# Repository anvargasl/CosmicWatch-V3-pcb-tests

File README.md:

# CosmicWatch_V3_RP

Handling versions of CosmicWatch pcb design, reusing V2 DC to DC booster and implementing new peak detection designa.

## CosmicWatch_detector_v30

main project, bringing together the different versions of parts desinged for peak detection and power.

### DC-DC-booster

Reimplementing CosmicWatch-V2 Dc to DC booster for lower noise in the power line.

### Peak-Detector

Latest peak detector circuit implemented for tests.

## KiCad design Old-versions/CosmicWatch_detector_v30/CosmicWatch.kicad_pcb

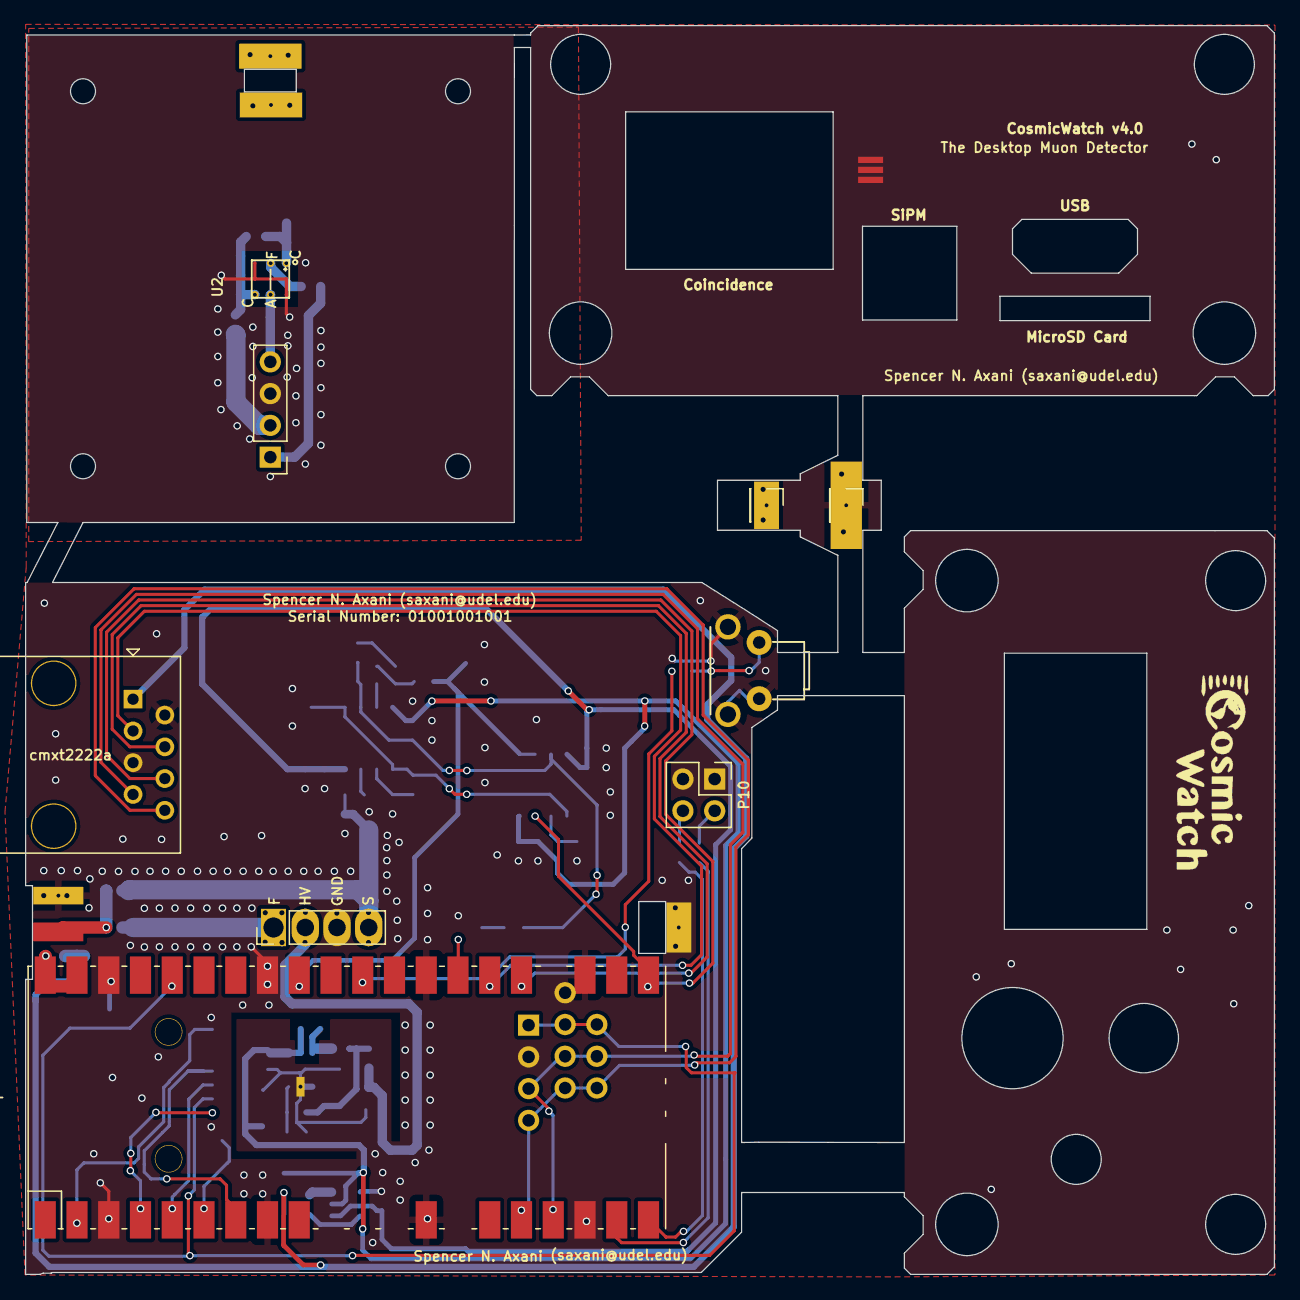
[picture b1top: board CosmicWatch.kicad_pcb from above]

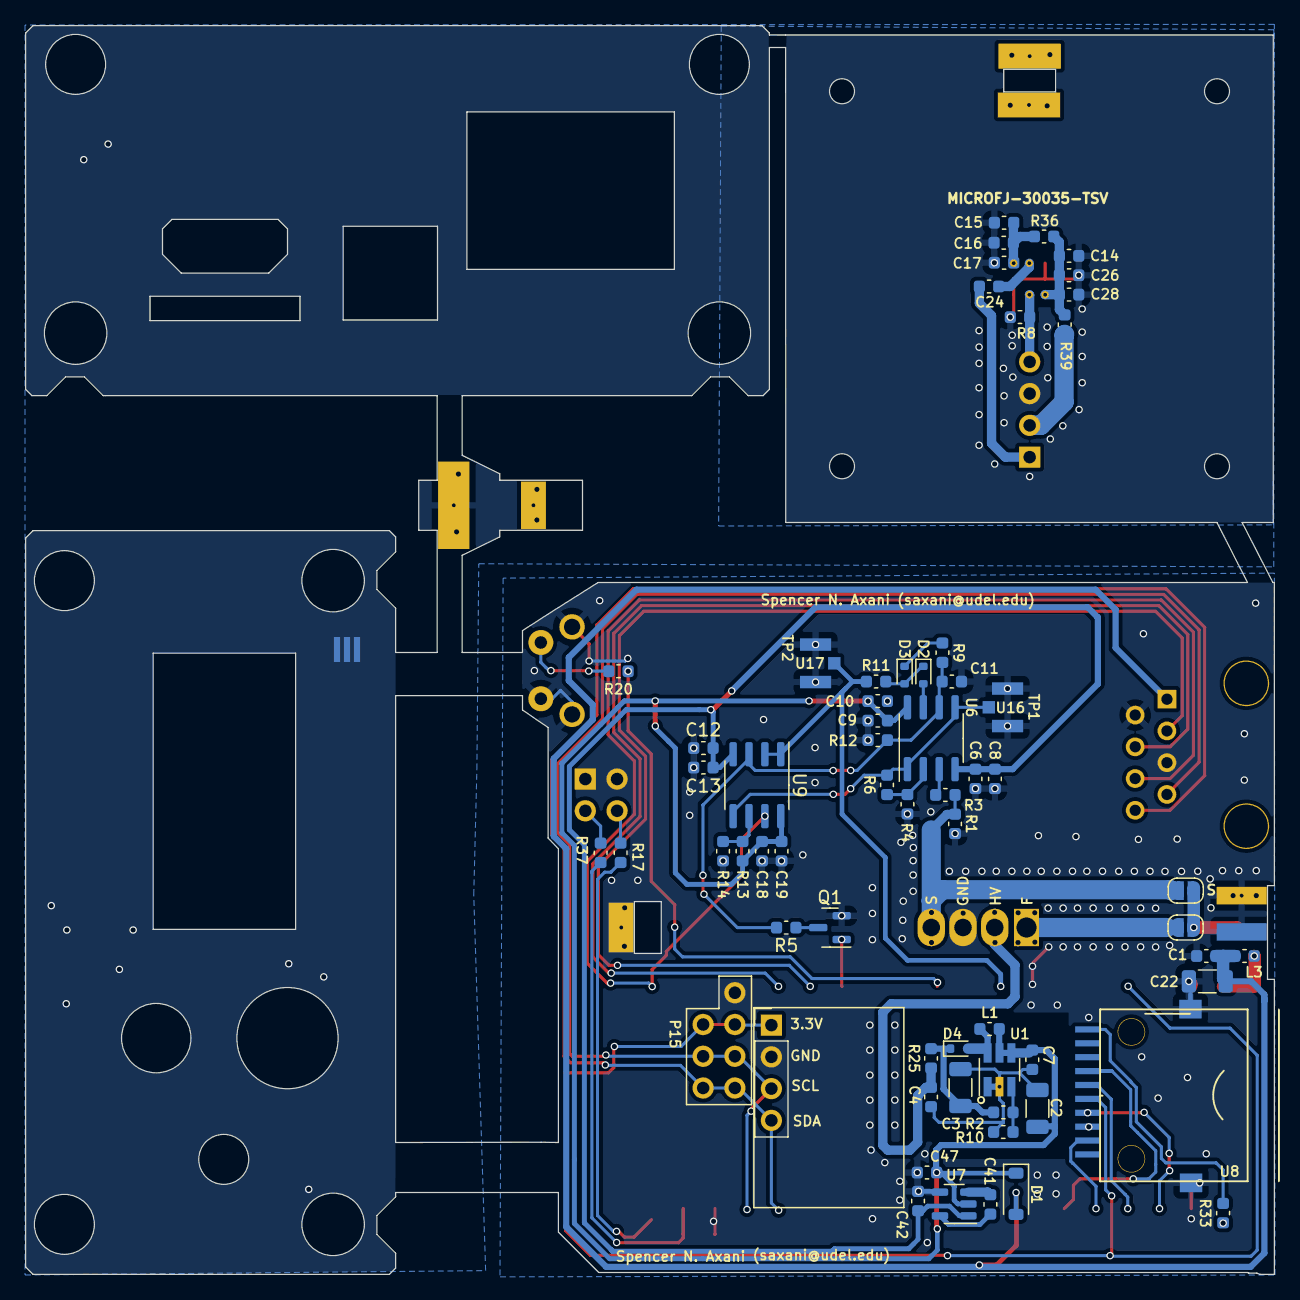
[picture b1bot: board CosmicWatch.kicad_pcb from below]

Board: 2 copper layers, 99.9 x 99.9 mm, 79 parts (65 on the bottom side), 49 nets.

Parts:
C1, C4, C47: 1uF; C_0603_1608Metric
C2: 4.7uF; C_1206_3216Metric
C3: 2.2uF; C_1206_3216Metric
C6, C12: 0.1uF; C_0603_1608Metric
C7, C8, C9, C13, C16, C18, C24, C26: 10nF; C_0603_1608Metric
C10, C19: 10n; C_0603_1608Metric
C11: 2nF; C_0603_1608Metric
C14, C17: 10p; C_0603_1608Metric
C15, C28: 100n; C_0603_1608Metric
C22: 6.8uF; C_1206_3216Metric
C41: C_0603_1608Metric
C42: 10uF; C_0603_1608Metric
D1: DIODE; D_SOD-123
D2, D3, D4: D_Schottky; D_SOD-523
J3: RJ45; RJ45_OST_PJ012-8P8CX_Vertical
L1: 15uH; C_0603_1608Metric
L3: INDUCTOR; C_0603_1608Metric
P1: CONN_01X04; PinHeader4_bigger_SiPM
P2: CONN_01X01; SiPM_PCB_Standoff
P3, P4: CONN_01X04; PinHeader_1x04_P2.54mm_Vertical
P5, P16: CONN_01X02; SolderJumper-2_P1.3mm_Open_RoundedPad1.0x1.5mm
P7, P8: CONN_01X01; GND_circle
P10: CONN_02X02; PinHeader_2x02_P2.54mm_Vertical
P11, P12, P13, P14: CONN_01X01; PinHeader_1x01_P2.54mm_Vertical
P15: CONN_02X04; PinHeader_2x04_P2.54mm_Vertical
P19: CONN_01X01; logo
Q1: 2N7002; SOT-23
R1: 47k; C_0603_1608Metric
R2: 147k; C_0603_1608Metric
R3: 49.9; C_0603_1608Metric
R4: 1k; C_0603_1608Metric
R5, R8, R36, R39: 10; C_0603_1608Metric
R6, R12, R13, R20, R33: 10k; C_0603_1608Metric
R9, R11, R14, R17, R25, R37: 100; C_0603_1608Metric
R10: 6.65k; C_0603_1608Metric
SW1: RESET; reset_button
U1: MAX5026; SOT-23-6_Handsoldering
U2: SiPM_MicroFJ−300XX−TSV
U3: MMCX; SMA_side_mount_sideways
U5: RasberryPi_Pico; RPi_Pico_SMD_TH_noThroughHoles
U6, U9: LMH6658; SOIC-8_3.9x4.9mm_P1.27mm
U7: TPS6040X; SOT-23-5
U8: sd_card_socket; sd_card
U16, U17: UMCC

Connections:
3.3V: P4.1, P15.3, P15.4, U5.36 (3v3_OUT), U8.4 (VCC)
AMP1: R6.1, U6.1 (OUTA), U6.5 (+INB), U9.5 (+INB), U16.1
CS: U5.7 (GP5), U8.2 (CS)
CoincidentPin1: J3.4, U5.25 (GP19)
CoincidentPin2: J3.3, U5.26 (GP20)
FAST: P1.1, P16.2
GNDA: C1.2, C2.2, C3.2, C4.2, C6.1, C7.1, C8.1, C9.2, C10.2, C11.1, C12.1, C13.1, C14.2, C15.2, C16.2, C17.2, C18.2, C19.2, C22.2, C26.2, C28.2, C42.2, C47.1, J3.2, J3.5, P1.3, P3.3, P4.2, P7.1, P8.1, P10.1, P10.3, P11.1, P14.1, P15.2, Q1.2 (S), R1.2, R4.2, R8.2, R10.1, R12.1, R14.1, SW1.1, U1.1 (PGND), U1.2 (GND), U2.A2 (GND), U2.A3 (GND), U2.C1 (GND), U2.C2 (GND), U3.2 (GND), U5.3 (GND), U5.8 (GND), U5.13 (GND), U5.18 (GND), U5.23 (GND), U5.28 (GND), U5.33 (AGND), U5.38 (GND), U7.4 (GND), U8.6 (GND), U16.2 (GND), U17.2 (GND)
HV: C4.1, P1.2, R25.1
MISO: U5.6 (GP4), U8.7 (D0)
MOSI: U5.5 (GP3), U8.3 (DI)
unnamed: C14.1, C26.1, C28.1, R36.2, R39.2, U2.A1 (C)
unnamed: C15.1, C16.1, C17.1, R36.1, U2.C3 (C)
unnamed: D2.2 (A), U6.7 (OUTB)
unnamed: D2.1 (K), D3.2 (A), R11.2
unnamed: D3.1 (K), R9.2
unnamed: D4.2 (A), L1.1, U1.6 (LX)
unnamed: C3.1, D4.1 (K), R2.2, R25.2
unnamed: C24.1, P3.1
unnamed: P3.2, R39.1
unnamed: P3.4, R8.1, U2.B1 (A)
unnamed: P10.2, R37.1
unnamed: P10.4, R17.2
unnamed: P5.1, P16.1, U3.1 (Sig)
unnamed: Q1.3 (D), R5.1
unnamed: R20.2, SW1.2
unnamed: R2.1, R10.2, U1.3 (FB)
unnamed: C24.2, U2.B3 (F)
unnamed: R37.2, U5.19 (GP14)
unnamed: R17.1, U5.20 (GP15)
unnamed: R20.1, U5.30 (RUN)
unnamed: R3.2, U6.3 (+INA)
unnamed: R4.1, R6.2, U6.2 (-INA)
unnamed: C11.2, R5.2, R9.1, R12.2, U6.6 (-INB), U9.3 (+INA)
unnamed: C41.1, U7.5 (Cfly+)
unnamed: C41.2, U7.3 (Cfly-)
unnamed: R33.2, U8.9 (Detect)
unnamed: R13.2, R14.2, U9.6 (-INB)
SCK: U5.4 (GP2), U8.5 (SCLK)
SCL: J3.7, P4.3, P15.5, P15.6, U5.17 (GP13)
SDA: J3.8, P4.4, P15.7, P15.8, U5.16 (GP12)
SENSE: R33.1, U5.2 (GP1)
SNG1: R11.1, U5.32 (ADC1), U9.1 (OUTA), U9.2 (-INA), U17.1
SiPM: P1.4, P5.2, R1.1, R3.1
TRG: J3.6, U5.21 (GP18), U9.7 (OUTB)
TriggerReset1: Q1.1 (G), U5.27 (GP21)
VBUS: C1.1, C22.1, D1.2 (K), J3.1, L3.1
VBat: L3.2, U5.39 (VSYS), U5.40 (VBus)
VCC: C2.1, C7.2, C9.1, C10.1, C18.1, C19.1, C47.2, D1.1 (A), L1.2, R13.1, U1.4 (SHDN), U1.5 (VCC), U6.8 (V+), U7.2 (IN), U9.8 (V+)
VEE: C6.2, C8.2, C12.2, C13.2, C42.1, U6.4 (V-), U7.1 (Out), U9.4 (V-)

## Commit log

2023-09-25 adding DC-DC booster on v3 schematics and pcb
2023-09-25 fixing misplaced VCC conection
2023-09-25 deleting original zip files from repo
2023-09-26 adding readme
2023-09-26 adding peak detector sketch, deleting misplaced folder
2023-09-26 adding new peak detector schematic
2023-09-27 rearranging DC-DC booster components
2023-09-30 adding Nuclear-Phoenix-inspired peak detector schematic
2023-10-02 new booster added
2023-10-02 removing second sipm
2023-10-02 adding peak detector and comparator
2023-10-02 fixing R13 resistance value
2023-10-03 removig old comparator
2023-10-03 moved MOSFET
2023-10-05 updating netlist and deleting unnecessary components from PCB
2023-10-05 rearranging peak detector in pcb
2023-10-06 placing peak detector
2023-10-08 finished peak detector placin and wiring, starting error corrections
2023-10-16 fixed errors, resized SiPM pcb
2023-10-17 adding some changes
2023-10-17 added R5 on trigger reset
2023-11-06 adding old peak detetion schematic
2023-11-20 optimizing some components
2023-11-27 adding update
2023-11-27 adddding
2023-11-30 New PCB design to test LT1807 with NPhoenix and CW V2 PD
2023-11-30 updating schematic pdf
2023-11-30 updating pcb
2023-11-30 updating cache
2023-12-05 updating CW v31 schematic pdf
2023-12-17 going back to TPS6040 for VEE, erasing unnecessary features from schematic
2023-12-19 fixing some component values
2023-12-19 deleting unnecessary folders
2023-12-19 rearranging old versions
2024-04-17 adding 3D printed case files
2024-05-09 adding power consumptioon data
2024-05-16 added power consumption and count rate plot and scripts
2024-05-16 adding power consumption and count rate plots
2024-05-24 fixing figure size and axis labels
2024-06-01 adding some adc calibration measurements
2024-06-05 adding code for ADC-voltage calibration
2024-06-12 no major changes
